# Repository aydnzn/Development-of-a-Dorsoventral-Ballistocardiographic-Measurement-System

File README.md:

# Internship Project: Development of a Dorsoventral Ballistocardiographic Measurement System

### Project Description
This project focuses on the development of a dorsoventral ballistocardiographic measurement system, specifically targeted at detecting ballistocardiographic impedance distortions in capacitive ECG. 

### Overview
This repository serves as the comprehensive archive of all the deliverables, artifacts, and insights gathered during my tenure as an intern at the [Medical Information Technology (MedIT), Helmholtz-Institute for Biomedical Engineering at RWTH Aachen University](https://www.medit.hia.rwth-aachen.de). The focus of my work centered around the design and development of capacitive ECG (cECG) and Ballistocardiography (BCG) systems, particularly exploring the nuances of human body's physiological vibrations and its impact on coupling impedance in cECG.

### Table of Contents
1. **Training_report.pdf** - This document encapsulates the cumulative learning and my detailed experience during the internship.
2. **./scripts** - This directory hosts all the Matlab scripts crafted for various analysis and computations.
3. **./photos** - A collection of photographs capturing significant moments and highlights of my internship journey.
4. **./figs** - This folder comprises of various visual representations, such as graphs and plots, created using Matlab for better understanding of problems, signals, and more.
5. **./data** - Preserved Matlab data files for future reference and use are stored here.
6. **./cnc_machine** - This section contains the necessary files required for operating the CNC machine which was instrumental in cutting the circuit boards.

### Contributors
This project was gracefully guided by [Mr. Uguz](https://ieeexplore.ieee.org/author/37086875617). I had the opportunity to develop the BCG measurement system, while my colleague, [Tuna](https://ieeexplore.ieee.org/author/37089188379), worked on the development of the impedance measurement system.

Our collaborative work, including my contributions, have been recognized and included in this [research paper](https://ieeexplore.ieee.org/document/8979354) authored by Mr. Uguz.

### License
This project is licensed under the terms of the MIT license.

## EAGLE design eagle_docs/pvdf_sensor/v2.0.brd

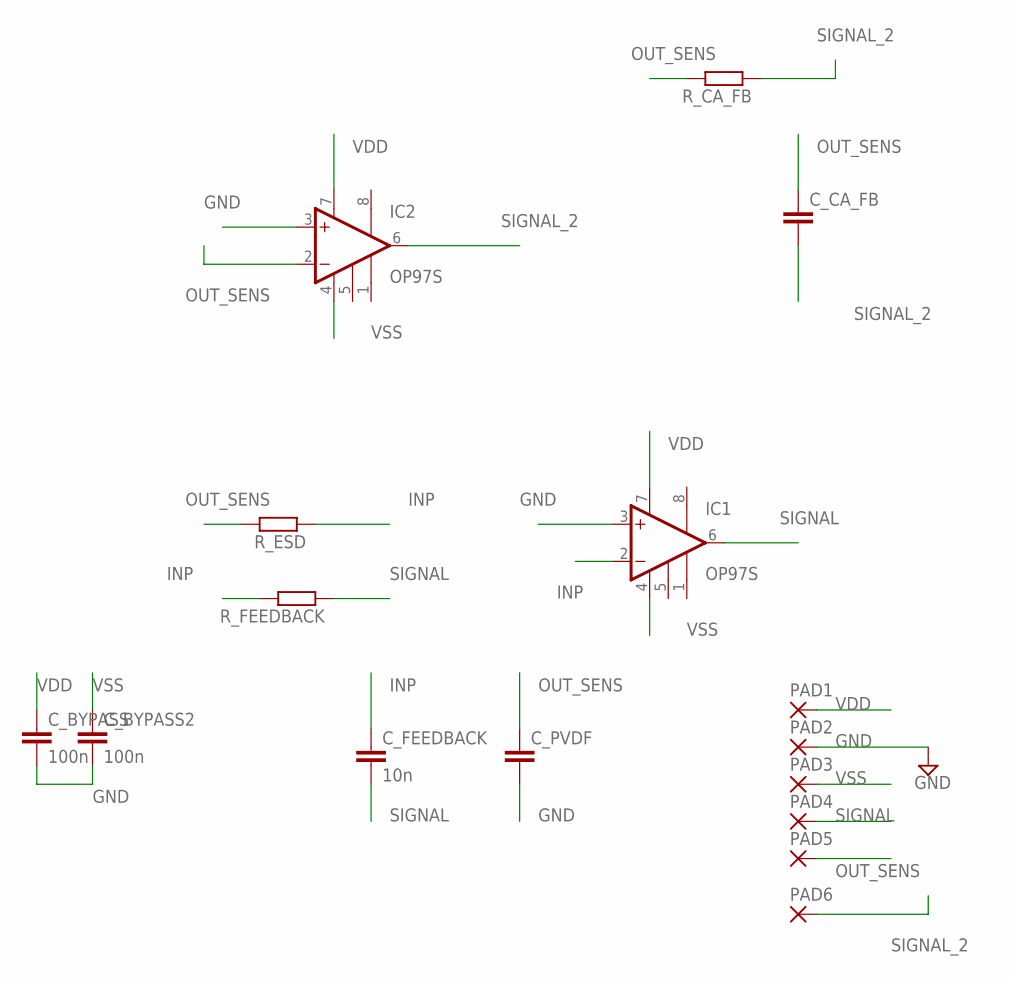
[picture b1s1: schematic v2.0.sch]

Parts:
C_BYPASS, C_BYPASS2: 100n; C0805
C_CA_FB: C-EUC0805; C0805
C_FEEDBACK: 10n; C0805
C_PVDF: C-EUC0805; C0805
IC1, IC2: OP97S; SO08
PAD1, PAD2, PAD3, PAD4, PAD5, PAD6: SMD5; SMD2,54-5,08
R_CA_FB: 10k; M0805
R_ESD: 5k; M0805
R_FEEDBACK: 100M; M0805

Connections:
GND: C_BYPASS.2, C_BYPASS2.2, C_PVDF.2, IC1.3 (+IN), IC2.3 (+IN), PAD2.1
INP: C_FEEDBACK.1, IC1.2 (-IN), R_ESD.1, R_FEEDBACK.2
OUT_SENS: C_CA_FB.1, C_PVDF.1, IC2.2 (-IN), PAD5.1, R_CA_FB.2, R_ESD.2
SIGNAL: C_FEEDBACK.2, IC1.6 (OUT), PAD4.1, R_FEEDBACK.1
SIGNAL_2: C_CA_FB.2, IC2.6 (OUT), PAD6.1, R_CA_FB.1
VDD: C_BYPASS.1, IC1.7 (V+), IC2.7 (V+), PAD1.1
VSS: C_BYPASS2.1, IC1.4 (V-), IC2.4 (V-), PAD3.1

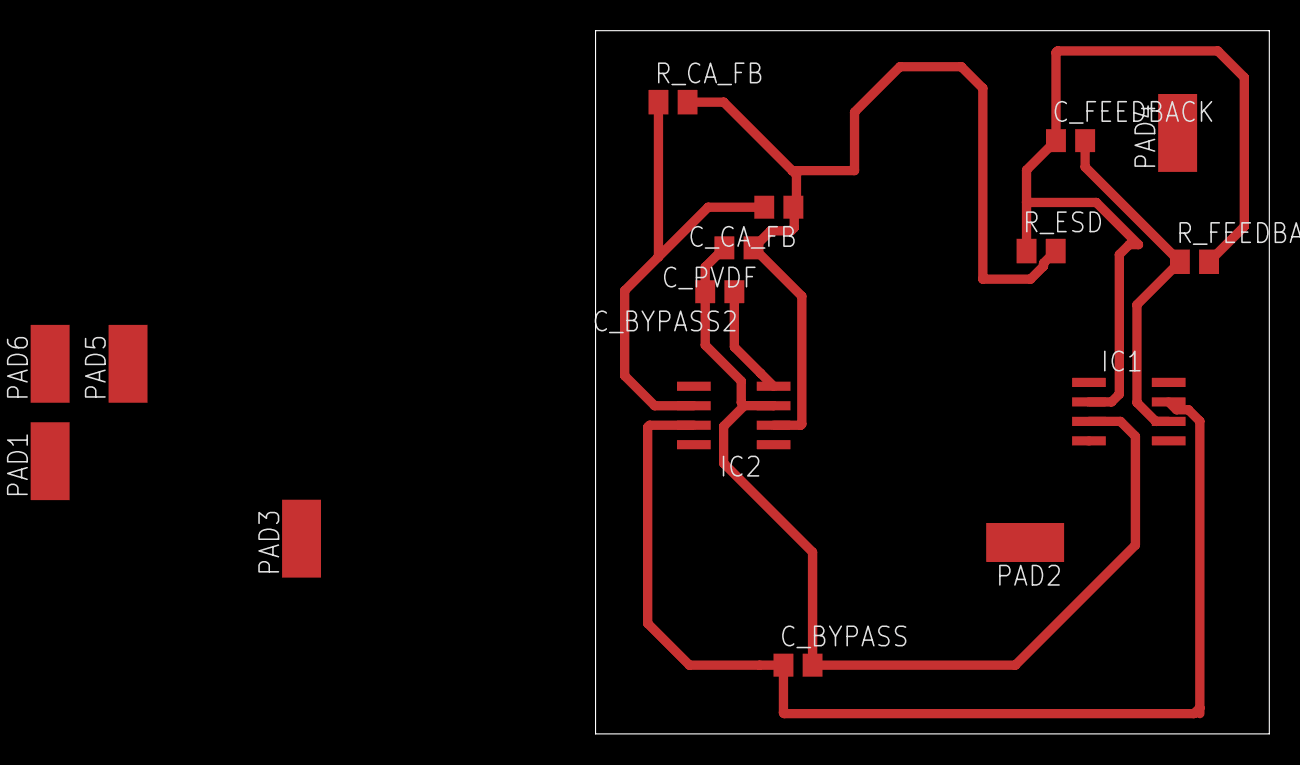
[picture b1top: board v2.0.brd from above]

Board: 2 copper layers, 43.9 x 45.9 mm, 16 parts (0 on the bottom side), 7 nets.

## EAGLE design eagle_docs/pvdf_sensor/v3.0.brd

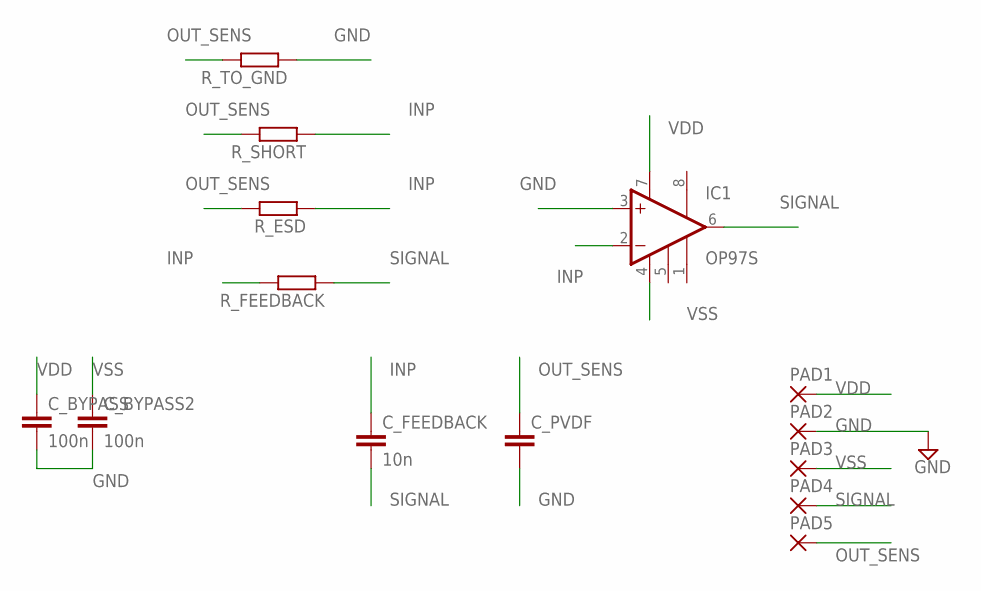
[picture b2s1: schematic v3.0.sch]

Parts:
C_BYPASS, C_BYPASS2: 100n; C0805
C_FEEDBACK: 10n; C0805
C_PVDF: C-EUC0805; C0805
IC1: OP97S; SO08
PAD1, PAD2, PAD3, PAD4, PAD5: SMD5; SMD2,54-5,08
R_ESD: 1M; M0805
R_FEEDBACK: 100M; M0805
R_SHORT: 1M; M0805
R_TO_GND: 1M; M0805

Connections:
GND: C_BYPASS.2, C_BYPASS2.2, C_PVDF.2, IC1.3 (+IN), PAD2.1, R_TO_GND.1
INP: C_FEEDBACK.1, IC1.2 (-IN), R_ESD.1, R_FEEDBACK.2, R_SHORT.1
OUT_SENS: C_PVDF.1, PAD5.1, R_ESD.2, R_SHORT.2, R_TO_GND.2
SIGNAL: C_FEEDBACK.2, IC1.6 (OUT), PAD4.1, R_FEEDBACK.1
VDD: C_BYPASS.1, IC1.7 (V+), PAD1.1
VSS: C_BYPASS2.1, IC1.4 (V-), PAD3.1

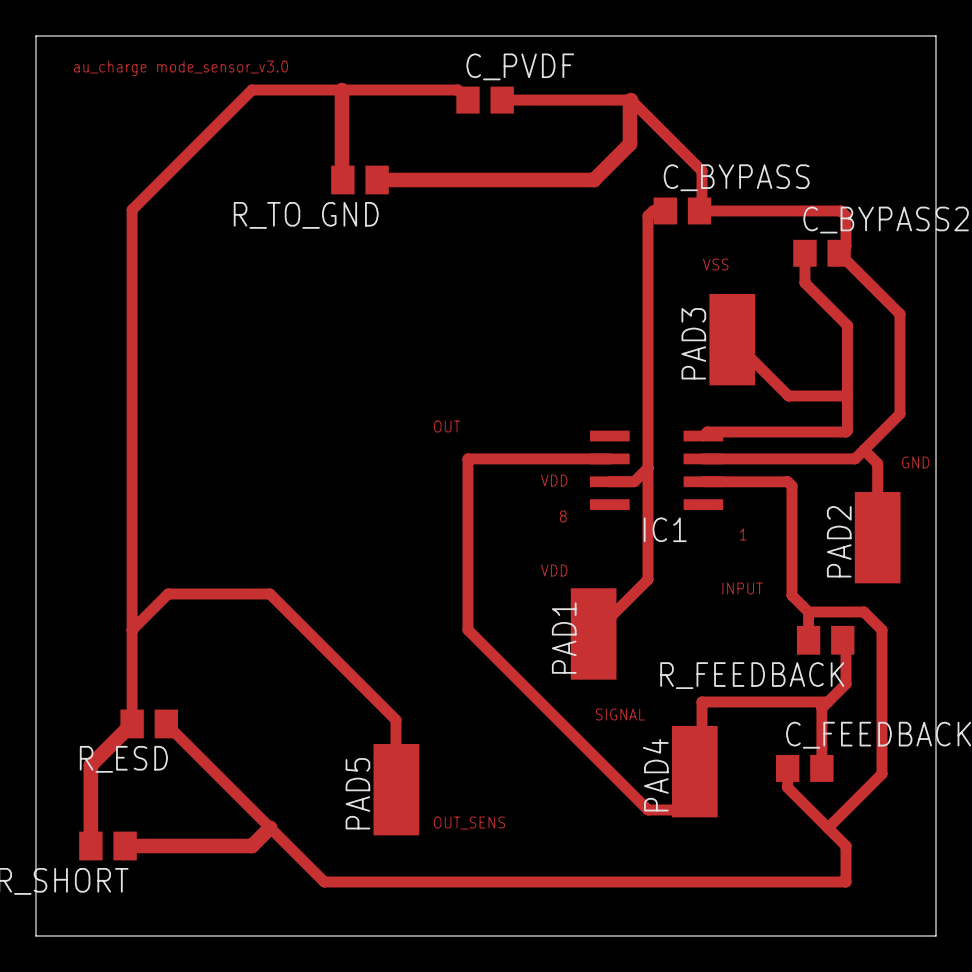
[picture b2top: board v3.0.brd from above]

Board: 2 copper layers, 50.0 x 50.0 mm, 14 parts (0 on the bottom side), 6 nets.

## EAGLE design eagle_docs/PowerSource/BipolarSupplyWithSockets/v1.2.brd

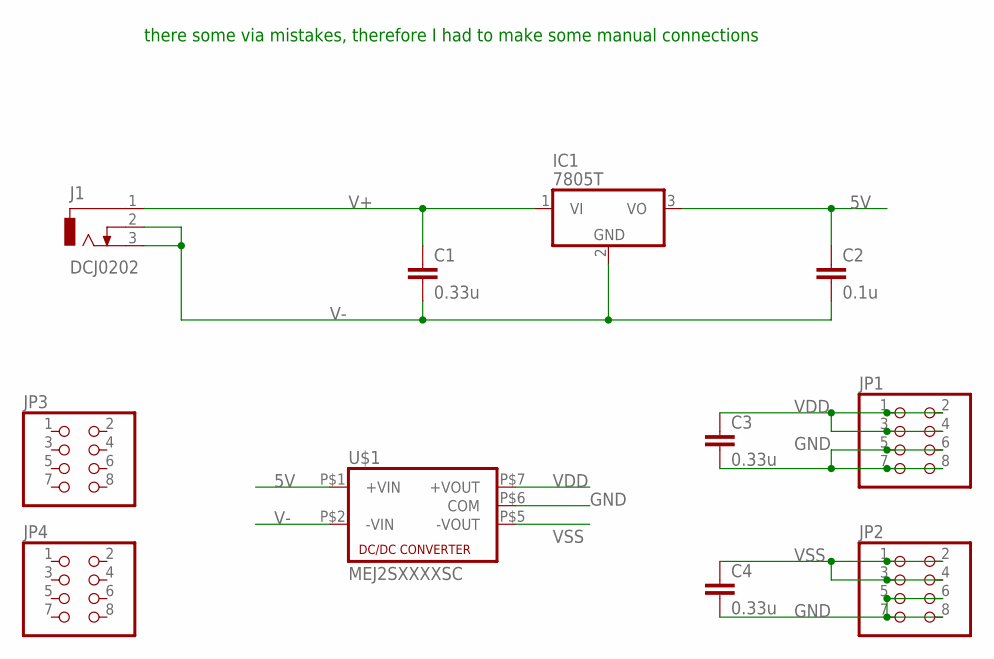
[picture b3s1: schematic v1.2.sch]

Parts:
C1, C3, C4: 0.33u; C050-045X075
C2: 0.1u; C050-045X075
IC1: 7805T; TO220H
J1: DCJ0202
JP1, JP2, JP3, JP4: PINHD-2X4; 2X04
U$1: MEJ2SXXXXSC; NMA

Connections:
5V: C2.1, IC1.3 (VO), U$1.P$1 (+VIN)
GND: C3.2, C4.2, JP1.5, JP1.6, JP1.7, JP1.8, JP2.5, JP2.6, JP2.7, JP2.8, U$1.P$6 (COM)
V+: C1.1, IC1.1 (VI), J1.1
V-: C1.2, C2.2, IC1.2 (GND), J1.2, J1.3, U$1.P$2 (-VIN)
VDD: C3.1, JP1.1, JP1.2, JP1.3, JP1.4, U$1.P$7 (+VOUT)
VSS: C4.1, JP2.1, JP2.2, JP2.3, JP2.4, U$1.P$5 (-VOUT)

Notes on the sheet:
there some via mistakes, therefore I had to make some manual connections

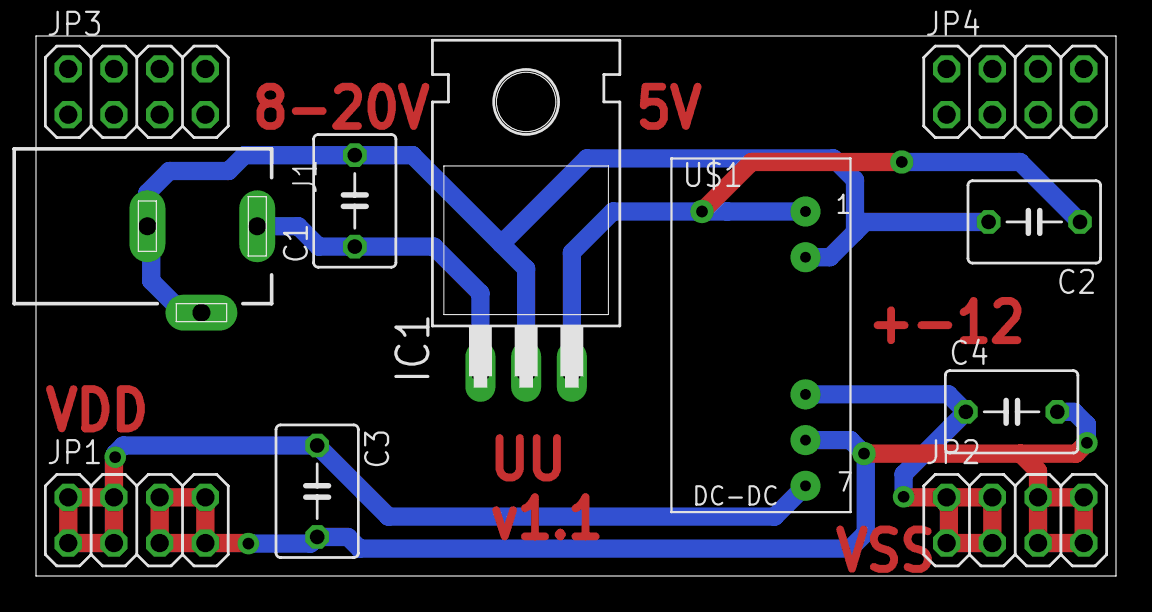
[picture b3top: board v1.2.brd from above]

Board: 2 copper layers, 60.0 x 30.0 mm, 11 parts (0 on the bottom side), 6 nets.

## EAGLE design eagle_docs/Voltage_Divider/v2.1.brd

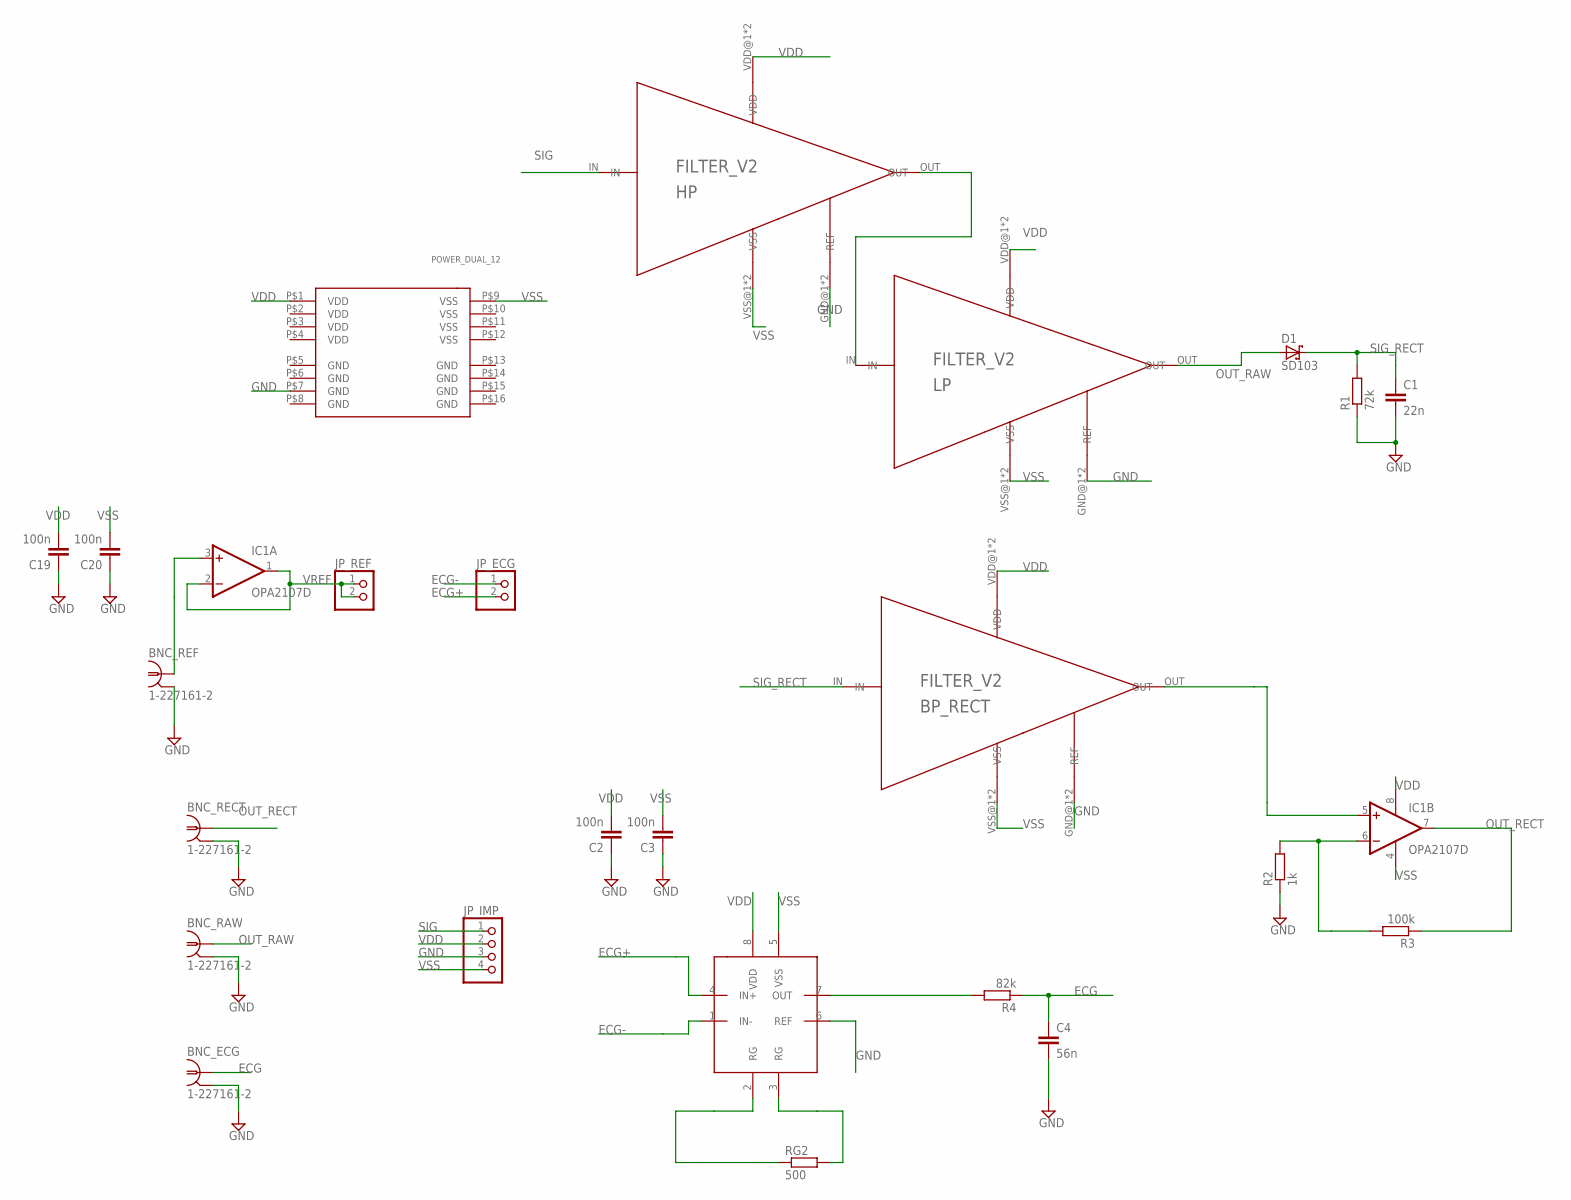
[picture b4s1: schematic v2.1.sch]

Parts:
BNC_ECG: 1-227161-2; AMP_227161
BNC_RAW: 1-227161-2; AMP_227161
BNC_RECT: 1-227161-2; AMP_227161
BNC_REF: 1-227161-2; AMP_227161
BP_RECT: FILTER_V2; MODULE_FILTER_V2
C1: 22n; C0805
C2, C3, C19, C20: 100n; C0805
C4: 56n; C0805
D1: SD103; DIODE_SMB
HP: FILTER_V2; MODULE_FILTER_V2
IC1: OPA2107D; SO08
INA: AD8429; SO8
JP_ECG: PINHD-1X2; 1X02
JP_IMP: PINHD-1X4; 1X04
JP_REF: PINHD-1X2; 1X02
LP: FILTER_V2; MODULE_FILTER_V2
R1: 72k; R0805
R2: 1k; R0805
R3: 100k; R0805
R4: 82k; R0805
RG2: 500; R0805
U$1: POWER_DUAL_12; MODULE_4X8

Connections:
ECG: BNC_ECG.1, C4.1, R4.1
ECG+: INA.4 (IN+), JP_ECG.2
ECG-: INA.1 (IN-), JP_ECG.1
GND: BNC_ECG.2, BNC_RAW.2, BNC_RECT.2, BNC_REF.2, BP_RECT.GND@1 (REF), BP_RECT.GND@2 (REF), C1.2, C2.1, C3.1, C4.2, C19.1, C20.1, HP.GND@1 (REF), HP.GND@2 (REF), INA.6 (REF), JP_IMP.3, LP.GND@1 (REF), LP.GND@2 (REF), R1.1, R2.1, U$1.P$7 (GND)
unnamed: IC1.6 (-IN), R2.2, R3.2
unnamed: BP_RECT.OUT, IC1.5 (+IN)
unnamed: INA.7 (OUT), R4.2
unnamed: HP.OUT, LP.IN
unnamed: BNC_REF.1, IC1.3 (+IN)
unnamed: INA.2 (RG), RG2.1
unnamed: INA.3 (RG), RG2.2
OUT_RAW: BNC_RAW.1, D1.A (C), LP.OUT
OUT_RECT: BNC_RECT.1, IC1.7 (OUT), R3.1
SIG: HP.IN, JP_IMP.1
SIG_RECT: BP_RECT.IN, C1.1, D1.C (A), R1.2
VDD: BP_RECT.VDD@1 (VDD), BP_RECT.VDD@2 (VDD), C2.2, C19.2, HP.VDD@1 (VDD), HP.VDD@2 (VDD), IC1.8 (V+), INA.8 (VDD), JP_IMP.2, LP.VDD@1 (VDD), LP.VDD@2 (VDD), U$1.P$1 (VDD)
VREF: IC1.1 (OUT), IC1.2 (-IN), JP_REF.1, JP_REF.2
VSS: BP_RECT.VSS@1 (VSS), BP_RECT.VSS@2 (VSS), C3.2, C20.2, HP.VSS@1 (VSS), HP.VSS@2 (VSS), IC1.4 (V-), INA.5 (VSS), JP_IMP.4, LP.VSS@1 (VSS), LP.VSS@2 (VSS), U$1.P$9 (VSS)

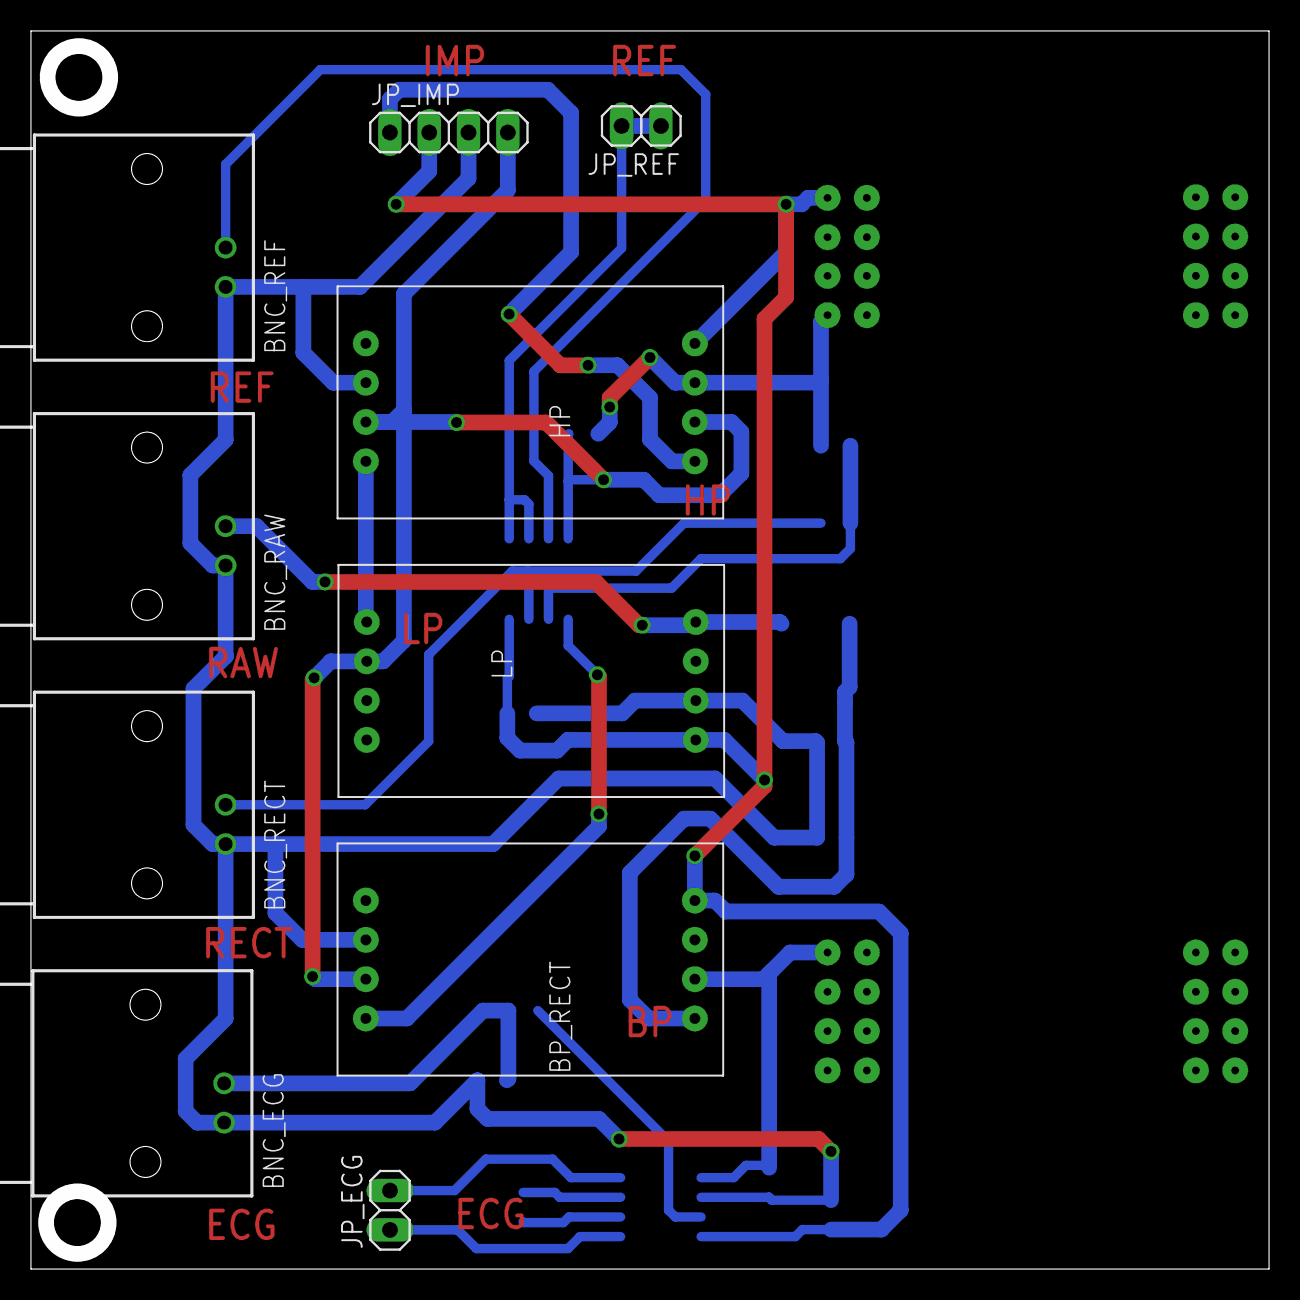
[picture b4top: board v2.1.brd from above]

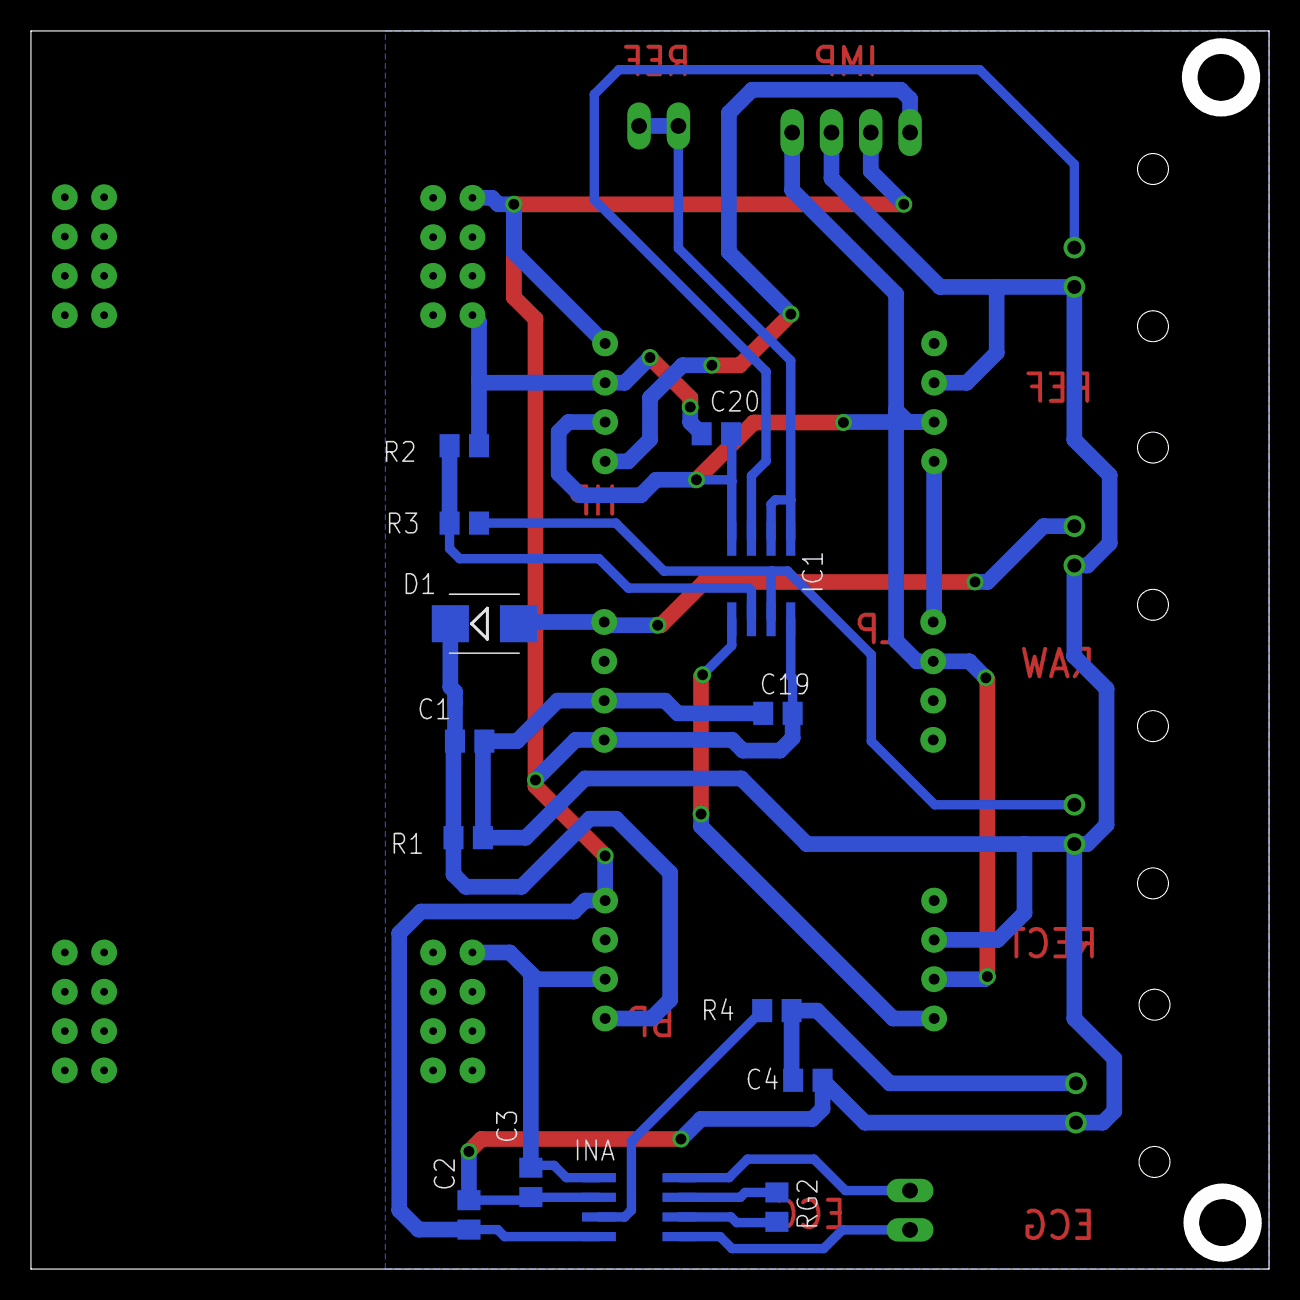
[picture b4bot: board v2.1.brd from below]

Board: 2 copper layers, 80.0 x 80.0 mm, 25 parts (14 on the bottom side), 18 nets.

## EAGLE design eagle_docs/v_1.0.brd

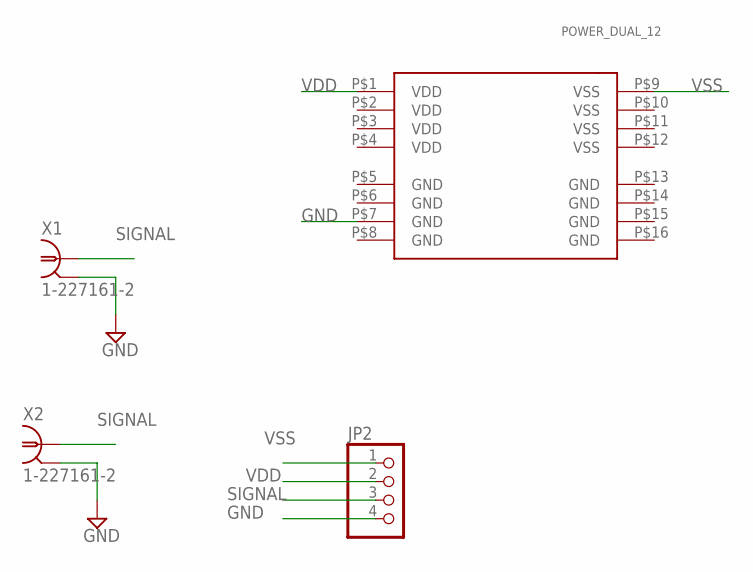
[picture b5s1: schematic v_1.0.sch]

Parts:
JP2: PINHD-1X4; 1X04
U$1: POWER_DUAL_12; MODULE_4X8
X1, X2: 1-227161-2; AMP_227161

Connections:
GND: JP2.4, U$1.P$7 (GND), X1.2, X2.2
SIGNAL: JP2.3, X1.1, X2.1
VDD: JP2.2, U$1.P$1 (VDD)
VSS: JP2.1, U$1.P$9 (VSS)

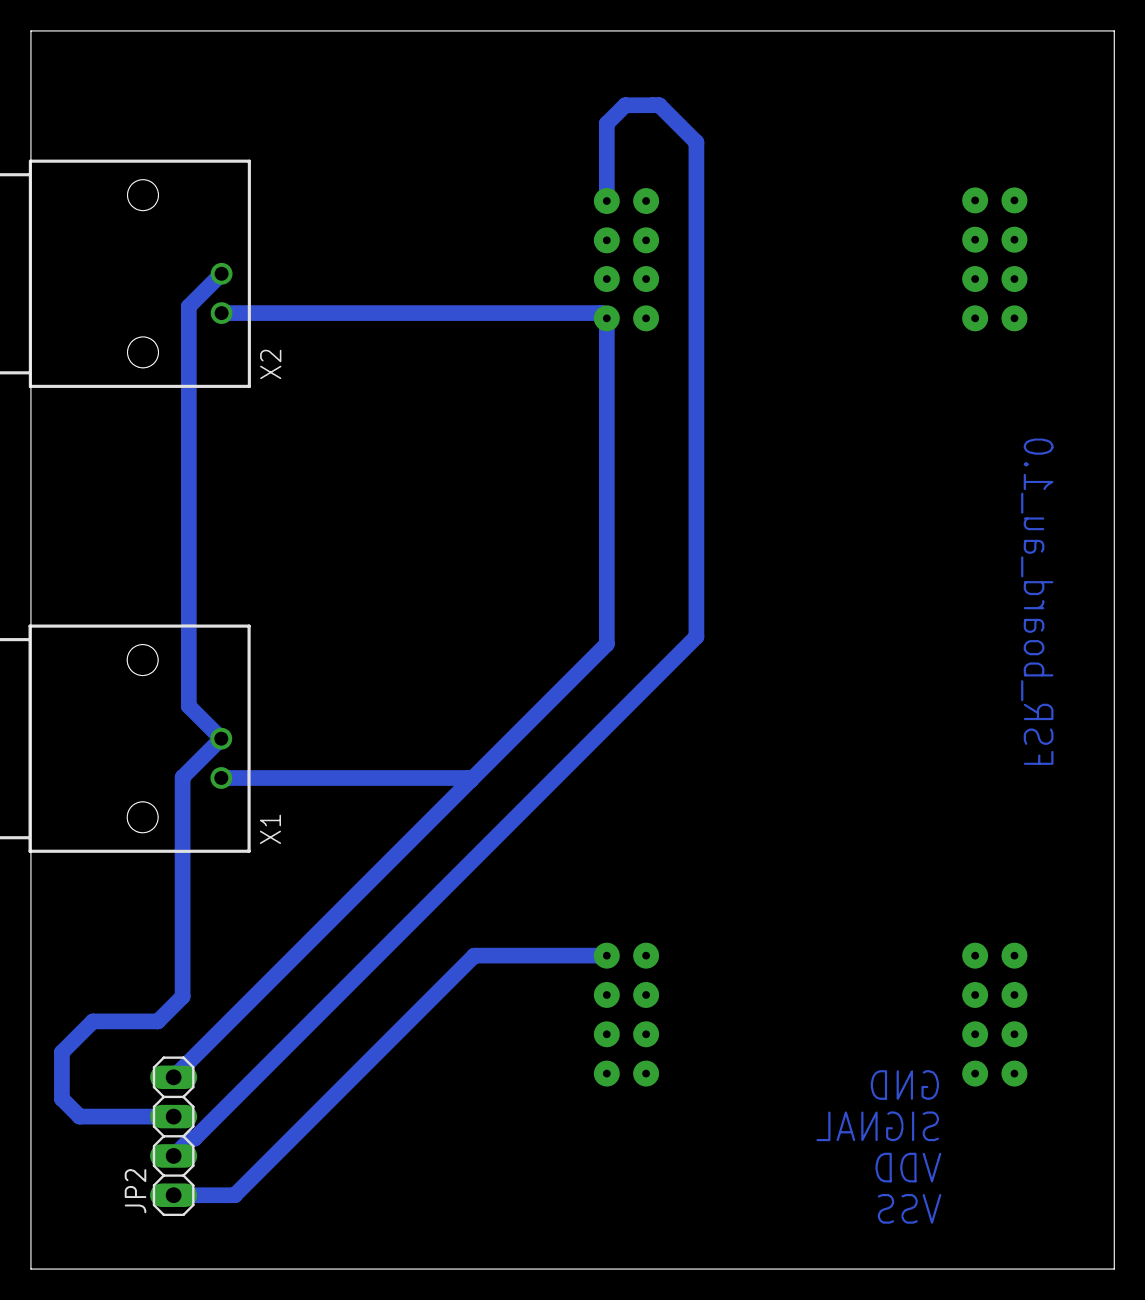
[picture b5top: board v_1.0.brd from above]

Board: 2 copper layers, 70.0 x 80.0 mm, 4 parts (0 on the bottom side), 4 nets.

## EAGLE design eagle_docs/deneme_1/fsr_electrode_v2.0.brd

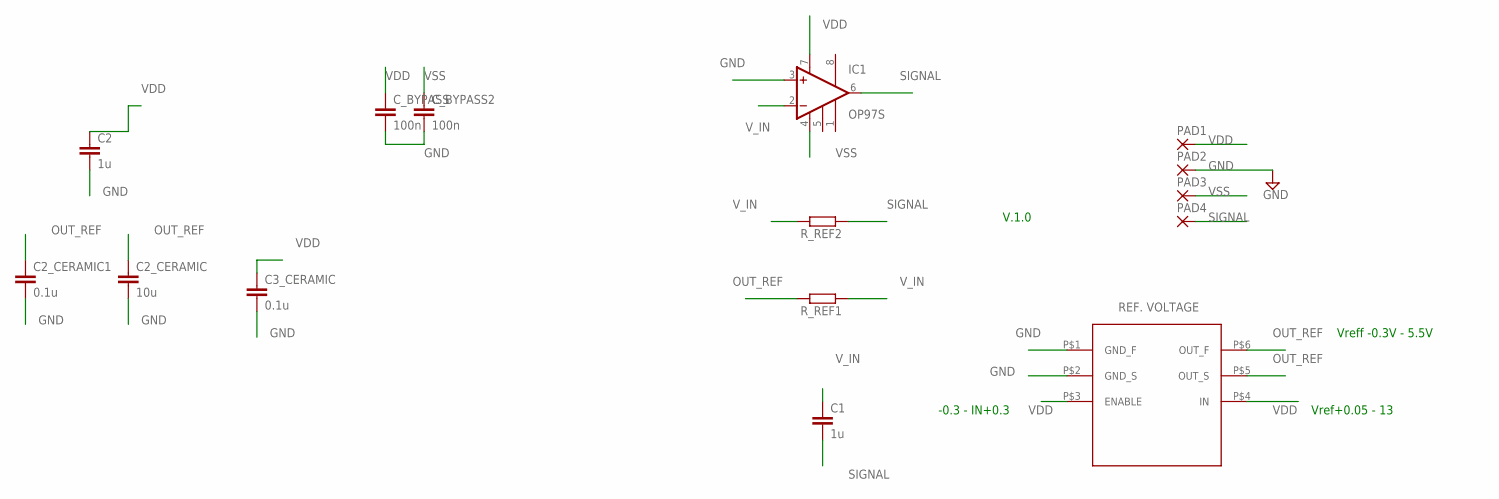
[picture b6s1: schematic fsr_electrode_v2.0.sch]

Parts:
C1, C2: 1u; C0805
C2_CERAMIC: 10u; C0805
C2_CERAMIC1, C3_CERAMIC: 0.1u; C0805
C_BYPASS, C_BYPASS2: 100n; C0805
IC1: OP97S; SO08
PAD1, PAD2, PAD3, PAD4: SMD5; SMD2,54-5,08
REF3450: REF3450IDBVR; UZUN
R_REF1, R_REF2: 10k; M0805

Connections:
GND: C2.2, C2_CERAMIC.2, C2_CERAMIC1.2, C3_CERAMIC.2, C_BYPASS.2, C_BYPASS2.2, IC1.3 (+IN), PAD2.1, REF3450.P$1 (GND_F), REF3450.P$2 (GND_S)
OUT_REF: C2_CERAMIC.1, C2_CERAMIC1.1, REF3450.P$5 (OUT_S), REF3450.P$6 (OUT_F), R_REF1.2
SIGNAL: C1.2, IC1.6 (OUT), PAD4.1, R_REF2.1
VDD: C2.1, C3_CERAMIC.1, C_BYPASS.1, IC1.7 (V+), PAD1.1, REF3450.P$3 (ENABLE), REF3450.P$4 (IN)
VSS: C_BYPASS2.1, IC1.4 (V-), PAD3.1
V_IN: C1.1, IC1.2 (-IN), R_REF1.1, R_REF2.2

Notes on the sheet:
V.1.0
Vref+0.05 - 13
-0.3 - IN+0.3
Vreff -0.3V - 5.5V

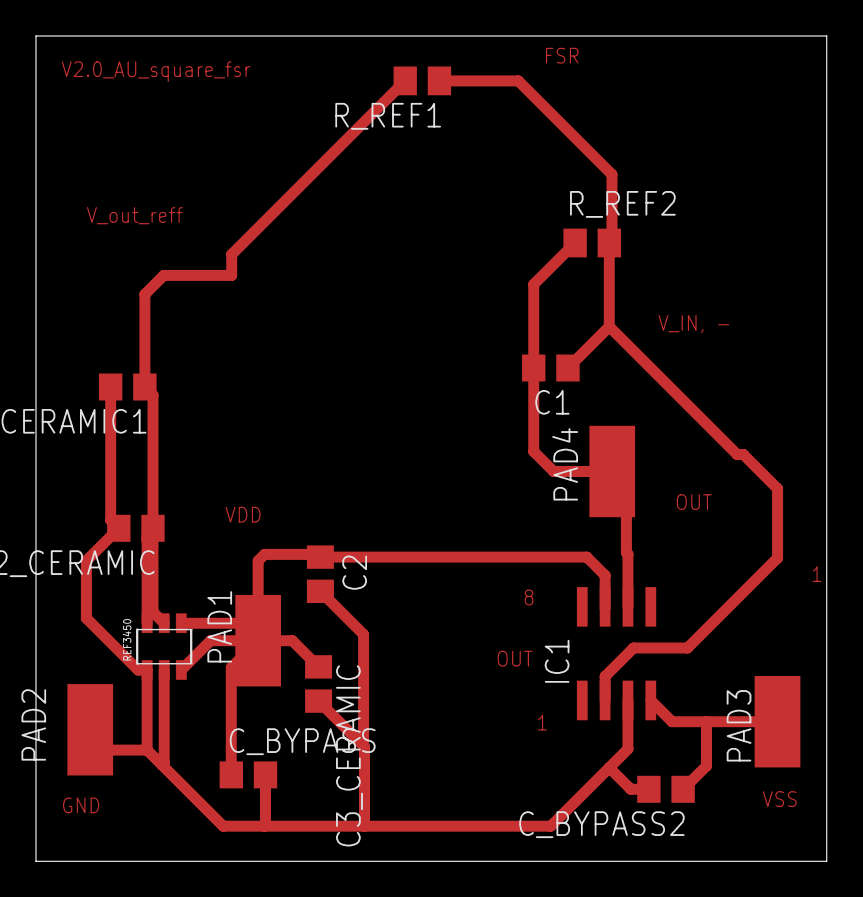
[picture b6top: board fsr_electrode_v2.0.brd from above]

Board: 2 copper layers, 43.9 x 45.9 mm, 15 parts (0 on the bottom side), 6 nets.

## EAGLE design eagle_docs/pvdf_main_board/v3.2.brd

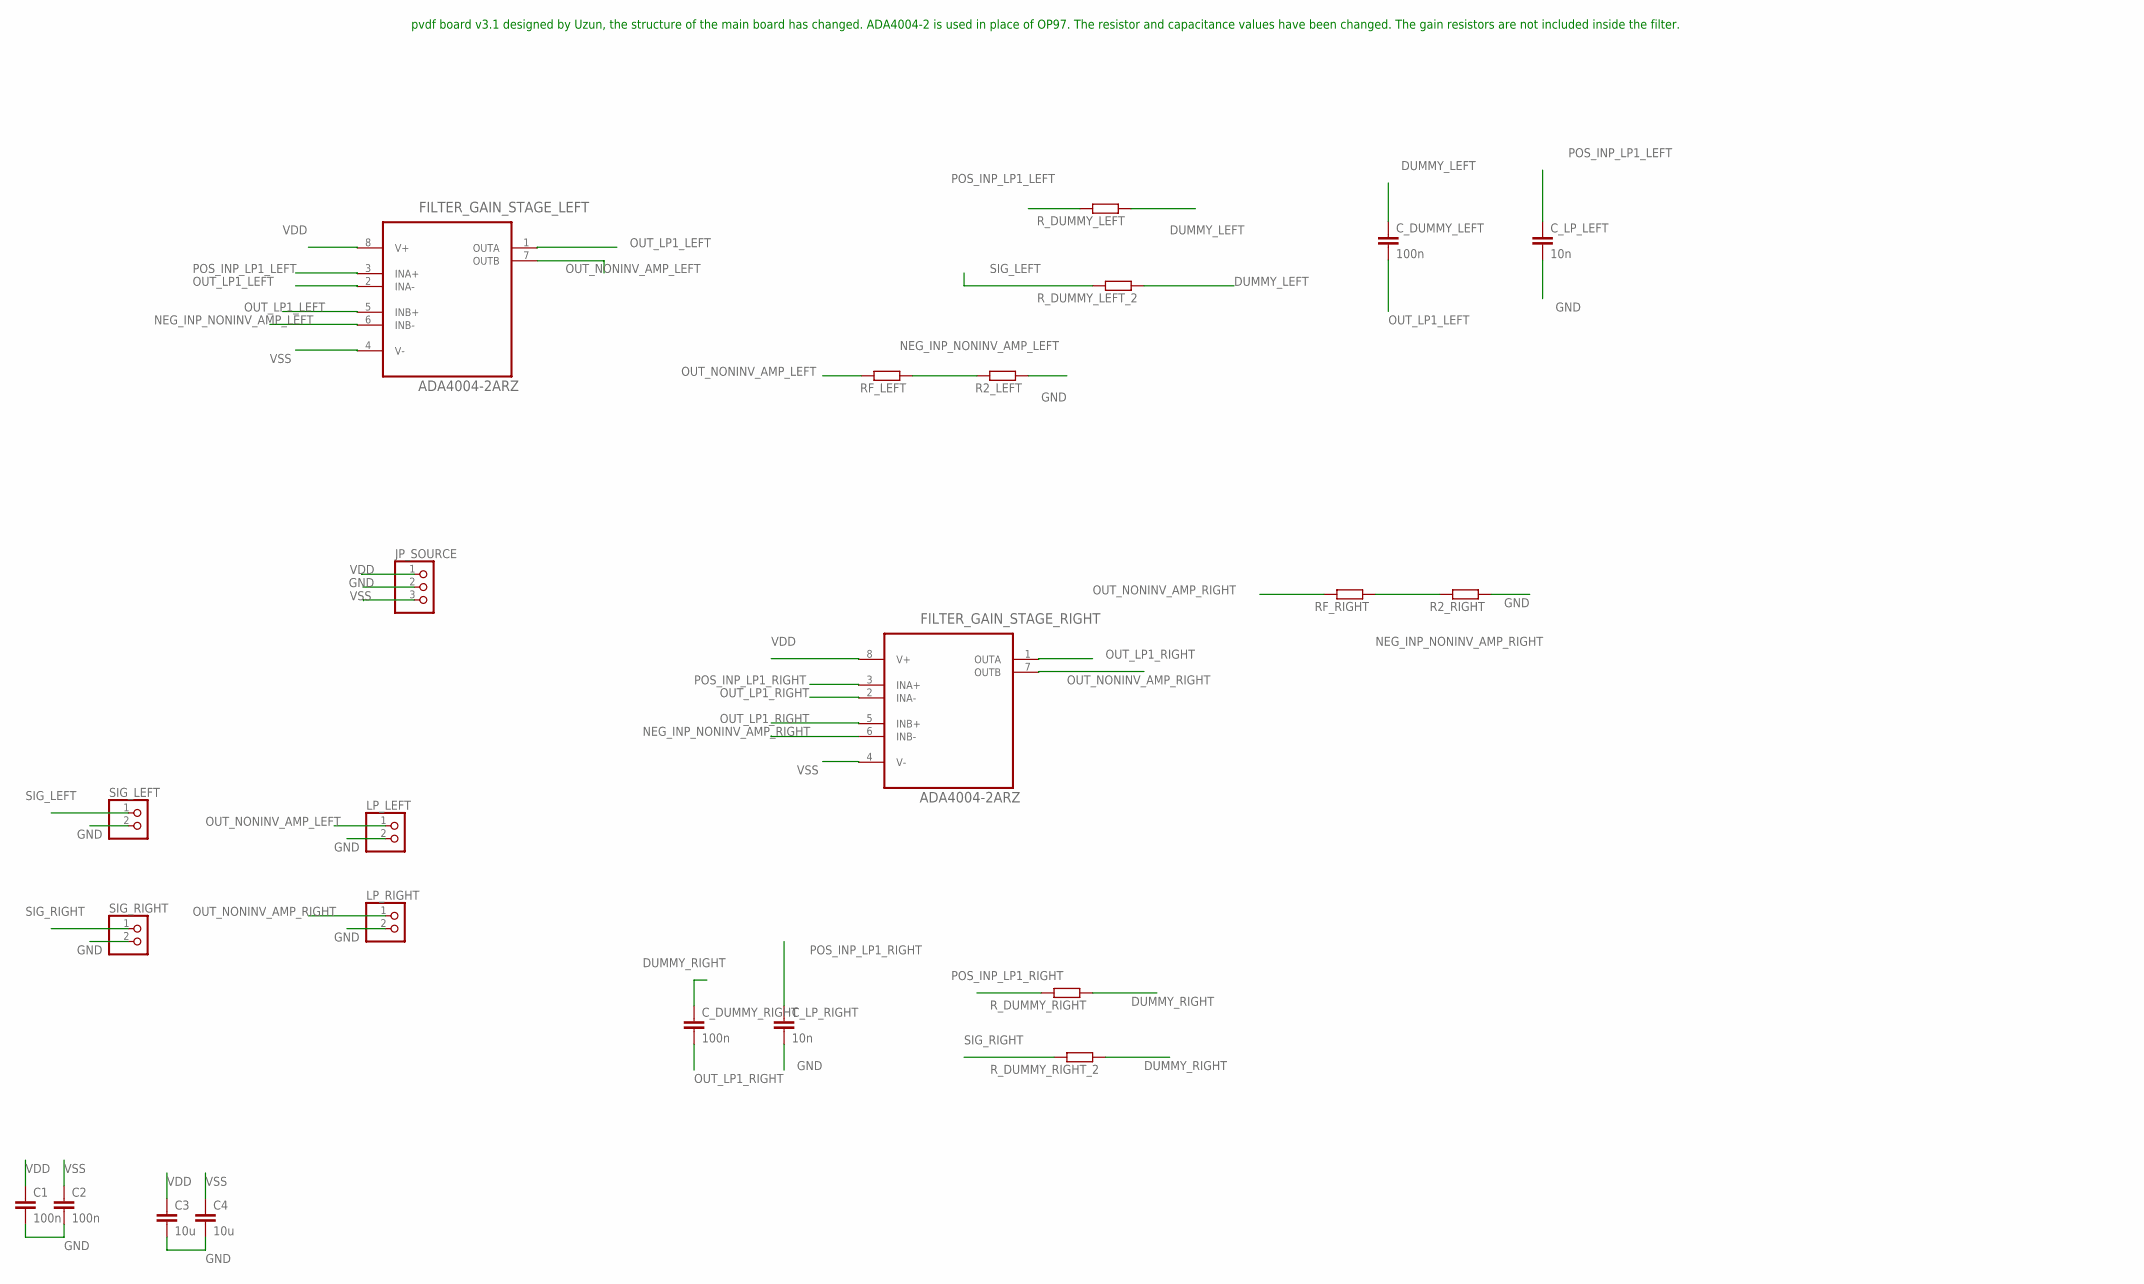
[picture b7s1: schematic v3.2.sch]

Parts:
C1, C2: 100n; C0805
C3, C4: 10u; C0805
C_DUMMY_LEFT: 100n; C0805
C_DUMMY_RIGHT: 100n; C0805
C_LP_LEFT: 10n; C0805
C_LP_RIGHT: 10n; C0805
FILTER_GAIN_STAGE_LEFT: ADA4004-2ARZ; SOIC127P600X175-8N
FILTER_GAIN_STAGE_RIGHT: ADA4004-2ARZ; SOIC127P600X175-8N
JP_SOURCE: PINHD-1X3; 1X03
LP_LEFT: PINHD-1X2; 1X02
LP_RIGHT: PINHD-1X2; 1X02
R2_LEFT, R2_RIGHT: 6.8k; M0805
RF_LEFT: 330k; M0805
RF_RIGHT: 330k; M0805
R_DUMMY_LEFT: 1M; M0805
R_DUMMY_LEFT_2: 68k; M0805
R_DUMMY_RIGHT: 1M; M0805
R_DUMMY_RIGHT_2: 68k; M0805
SIG_LEFT: PINHD-1X2; 1X02
SIG_RIGHT: PINHD-1X2; 1X02

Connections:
DUMMY_LEFT: C_DUMMY_LEFT.1, R_DUMMY_LEFT.1, R_DUMMY_LEFT_2.1
DUMMY_RIGHT: C_DUMMY_RIGHT.1, R_DUMMY_RIGHT.1, R_DUMMY_RIGHT_2.1
GND: C1.2, C2.2, C3.2, C4.2, C_LP_LEFT.2, C_LP_RIGHT.2, JP_SOURCE.2, LP_LEFT.2, LP_RIGHT.2, R2_LEFT.1, R2_RIGHT.1, SIG_LEFT.2, SIG_RIGHT.2
NEG_INP_NONINV_AMP_LEFT: FILTER_GAIN_STAGE_LEFT.6 (INB-), R2_LEFT.2, RF_LEFT.1
NEG_INP_NONINV_AMP_RIGHT: FILTER_GAIN_STAGE_RIGHT.6 (INB-), R2_RIGHT.2, RF_RIGHT.1
OUT_LP1_LEFT: C_DUMMY_LEFT.2, FILTER_GAIN_STAGE_LEFT.1 (OUTA), FILTER_GAIN_STAGE_LEFT.2 (INA-), FILTER_GAIN_STAGE_LEFT.5 (INB+)
OUT_LP1_RIGHT: C_DUMMY_RIGHT.2, FILTER_GAIN_STAGE_RIGHT.1 (OUTA), FILTER_GAIN_STAGE_RIGHT.2 (INA-), FILTER_GAIN_STAGE_RIGHT.5 (INB+)
OUT_NONINV_AMP_LEFT: FILTER_GAIN_STAGE_LEFT.7 (OUTB), LP_LEFT.1, RF_LEFT.2
OUT_NONINV_AMP_RIGHT: FILTER_GAIN_STAGE_RIGHT.7 (OUTB), LP_RIGHT.1, RF_RIGHT.2
POS_INP_LP1_LEFT: C_LP_LEFT.1, FILTER_GAIN_STAGE_LEFT.3 (INA+), R_DUMMY_LEFT.2
POS_INP_LP1_RIGHT: C_LP_RIGHT.1, FILTER_GAIN_STAGE_RIGHT.3 (INA+), R_DUMMY_RIGHT.2
SIG_LEFT: R_DUMMY_LEFT_2.2, SIG_LEFT.1
SIG_RIGHT: R_DUMMY_RIGHT_2.2, SIG_RIGHT.1
VDD: C1.1, C3.1, FILTER_GAIN_STAGE_LEFT.8 (V+), FILTER_GAIN_STAGE_RIGHT.8 (V+), JP_SOURCE.1
VSS: C2.1, C4.1, FILTER_GAIN_STAGE_LEFT.4 (V-), FILTER_GAIN_STAGE_RIGHT.4 (V-), JP_SOURCE.3

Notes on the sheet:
pvdf board v3.1 designed by Uzun, the structure of the main board has changed. ADA4004-2 is used in place of OP97. The resistor and capacitance values have been changed. The gain resistors are not included inside the filter.

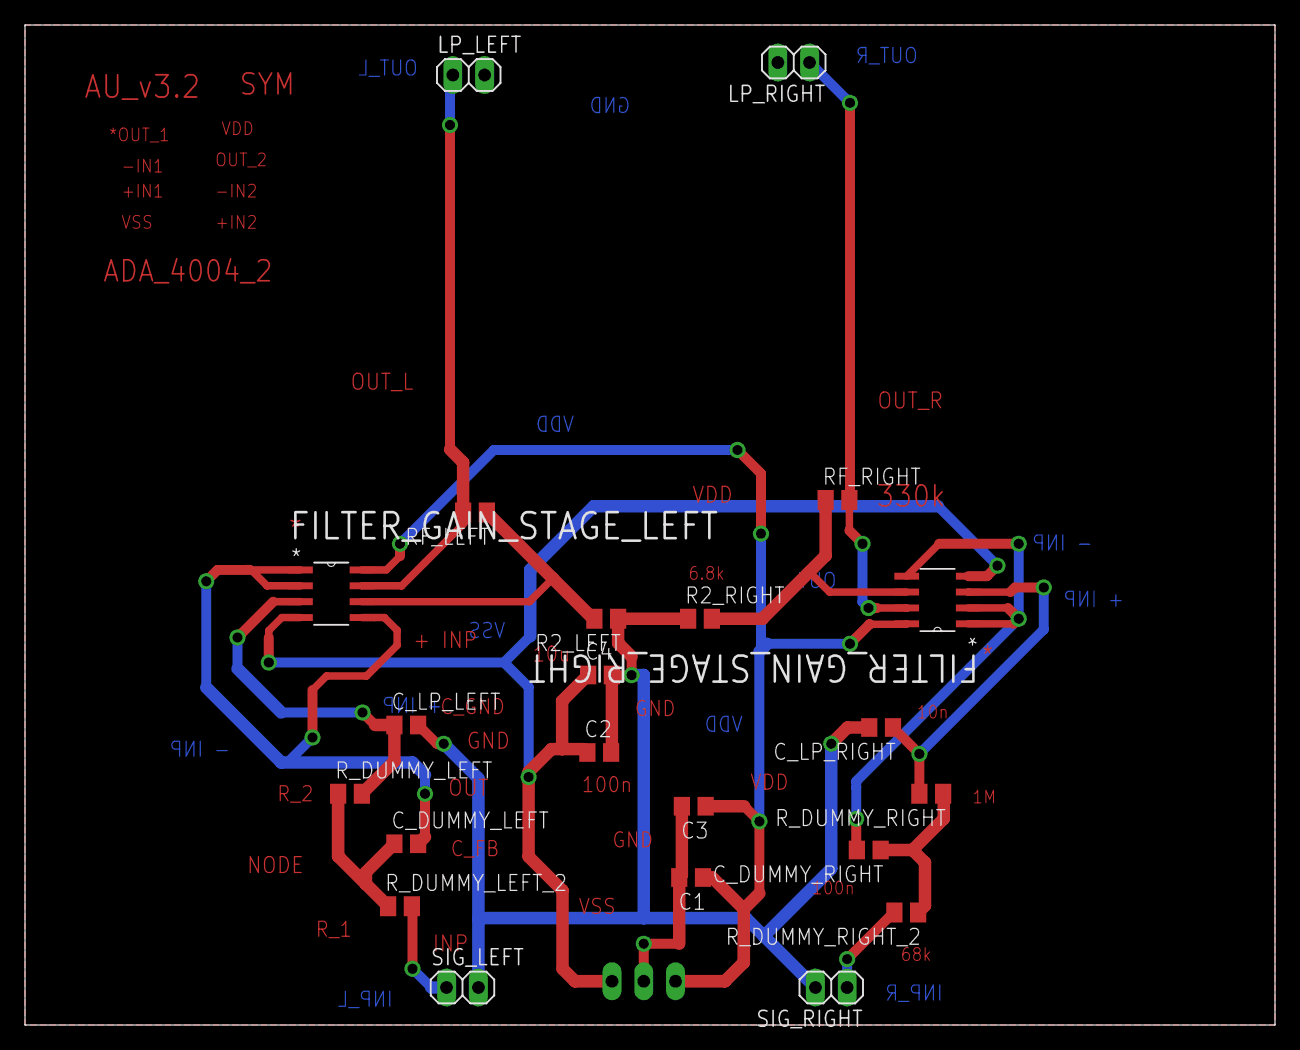
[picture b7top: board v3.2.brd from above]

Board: 2 copper layers, 100.0 x 80.0 mm, 23 parts (1 on the bottom side), 15 nets.
